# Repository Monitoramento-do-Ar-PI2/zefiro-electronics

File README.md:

# Zefiro electronics
This is the electronic team repository, here you can find the development of embedded system codes, eletronic schematics and pcb layouts.

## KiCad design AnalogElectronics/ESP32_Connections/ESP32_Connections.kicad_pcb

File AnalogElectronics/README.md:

<h1 align="center">
      Eletrônica Analógica Zéfiro
</h1>

<p align="justify">
      A eletrônica analógica é aplicada na estação de monitoramento de ar Zéfiro, sendo um sistema de instrumentação eletrônica modular, onde seus componentes são distríbuidos no melhor posicionamento para seu uso e as ligações realizadas, por meio de cabos, com a central de controle, utilizando o microcontrolador ESP32.

 - **Esquemático Geral** O esquemático geral representa todos os módulos e suas conexões entre si, enquanto cada pasta tem o desenvolvimento individual do esqumático e layout de pcb destes módulos.

  #### Desenvolvedores:
  Clara Justa
  
  Débora Janini
  
  Felipe Alcântara

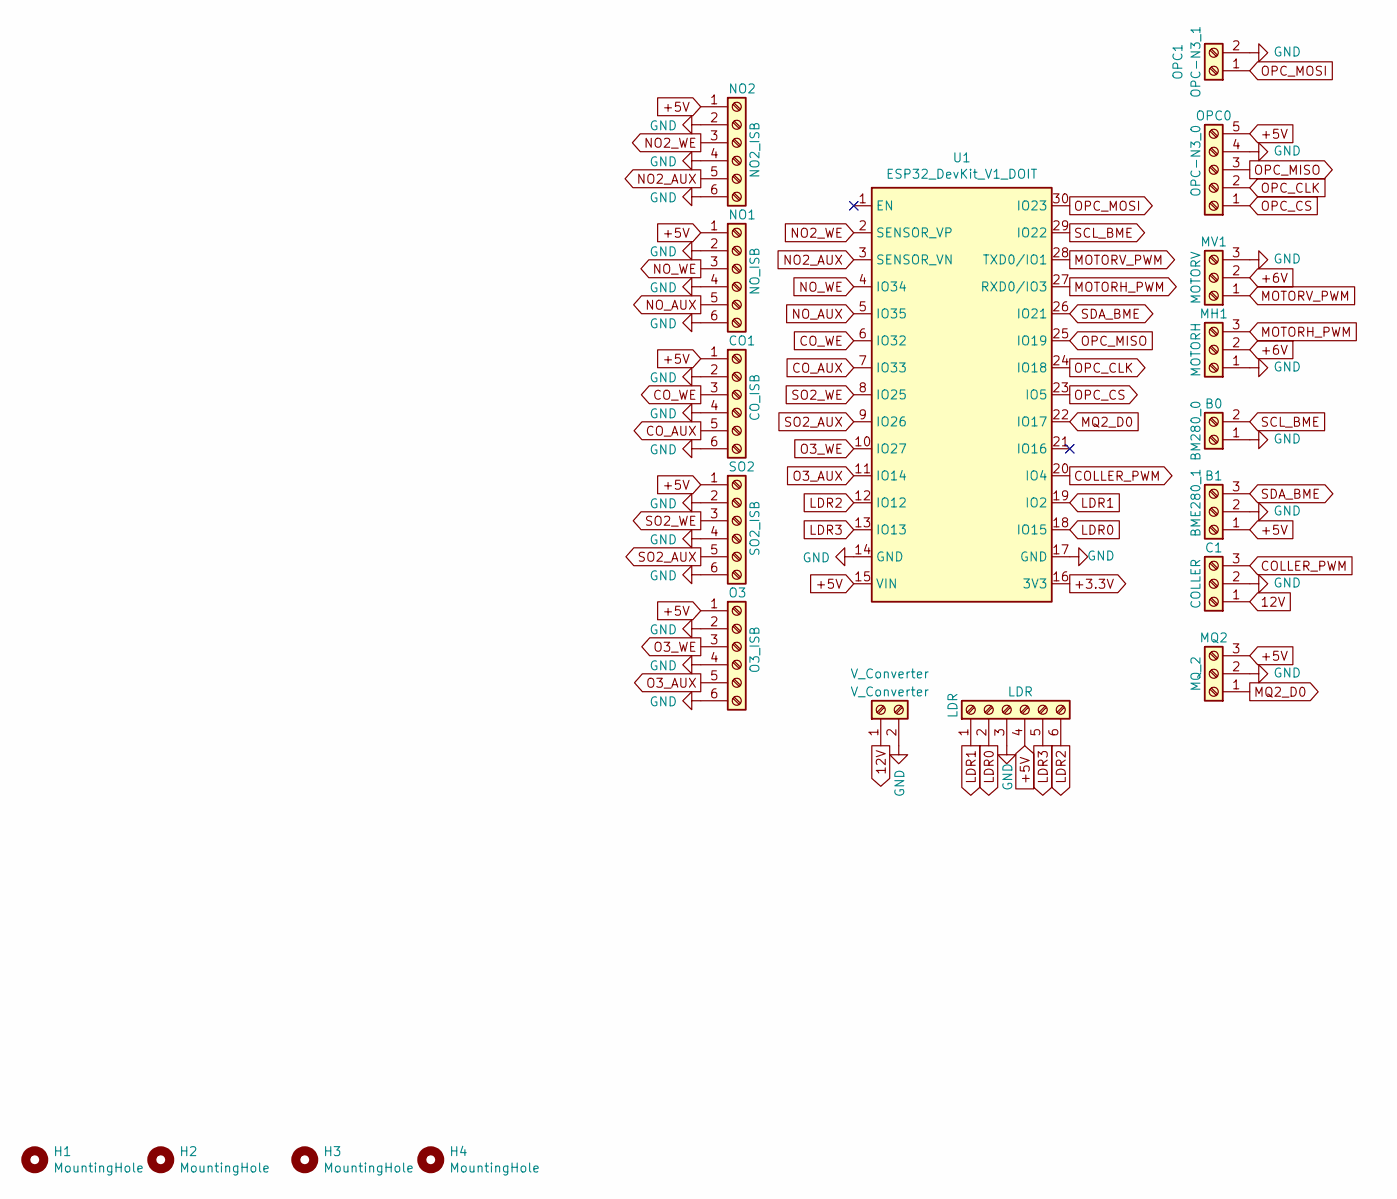
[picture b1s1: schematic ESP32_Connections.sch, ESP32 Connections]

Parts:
B0: BM280_0; Molex_KK-254_AE-6410-02A_1x02_P2.54mm_Vertical
B1: BME280_1; Molex_KK-254_AE-6410-03A_1x03_P2.54mm_Vertical
C1: COLLER; Molex_KK-254_AE-6410-03A_1x03_P2.54mm_Vertical
CO1: CO_ISB; Molex_KK-254_AE-6410-06A_1x06_P2.54mm_Vertical
H1, H2, H3, H4: MountingHole; MountingHole_3mm
LDR: LDR; Molex_KK-254_AE-6410-06A_1x06_P2.54mm_Vertical
MH1: MOTORH; Molex_KK-254_AE-6410-03A_1x03_P2.54mm_Vertical
MQ2: MQ_2; Molex_KK-254_AE-6410-03A_1x03_P2.54mm_Vertical
MV1: MOTORV; Molex_KK-254_AE-6410-03A_1x03_P2.54mm_Vertical
NO1: NO_ISB; Molex_KK-254_AE-6410-06A_1x06_P2.54mm_Vertical
NO2: NO2_ISB; Molex_KK-254_AE-6410-06A_1x06_P2.54mm_Vertical
O3: O3_ISB; Molex_KK-254_AE-6410-06A_1x06_P2.54mm_Vertical
OPC0: OPC-N3_0; Molex_KK-254_AE-6410-05A_1x05_P2.54mm_Vertical
OPC1: OPC-N3_1; Molex_KK-254_AE-6410-02A_1x02_P2.54mm_Vertical
SO2: SO2_ISB; Molex_KK-254_AE-6410-06A_1x06_P2.54mm_Vertical
U1: ESP32_DevKit_V1_DOIT; esp32_devkit_v1_doit
V_Converter: V_Converter; Molex_KK-254_AE-6410-02A_1x02_P2.54mm_Vertical

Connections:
12V: C1.1, V_Converter.1; also elsewhere on the board
+3.3V: U1.16 (3V3)
COLLER_PWM: C1.3, U1.20 (IO4)
CO_AUX: CO1.5, U1.7 (IO33)
CO_WE: CO1.3, U1.6 (IO32)
GND: B0.1, B1.2, C1.2, CO1.2, CO1.4, CO1.6, LDR.3, MH1.1, MQ2.2, MV1.3, NO1.2, NO1.4, NO1.6, NO2.2, NO2.4, NO2.6, O3.2, O3.4, O3.6, OPC0.4, OPC1.2, SO2.2, SO2.4, SO2.6, U1.14 (GND), U1.17 (GND), V_Converter.2; also elsewhere on the board
LDR0: LDR.2, U1.18 (IO15); also elsewhere on the board
LDR1: LDR.1, U1.19 (IO2); also elsewhere on the board
LDR2: LDR.6, U1.12 (IO12); also elsewhere on the board
LDR3: LDR.5, U1.13 (IO13); also elsewhere on the board
MOTORH_PWM: MH1.3, U1.27 (RXD0/IO3)
MOTORV_PWM: MV1.1, U1.28 (TXD0/IO1)
MQ2_D0: MQ2.1, U1.22 (IO17)
NO2_AUX: NO2.5, U1.3 (SENSOR_VN)
NO2_WE: NO2.3, U1.2 (SENSOR_VP)
NO_AUX: NO1.5, U1.5 (IO35)
NO_WE: NO1.3, U1.4 (IO34)
O3_AUX: O3.5, U1.11 (IO14)
O3_WE: O3.3, U1.10 (IO27)
OPC_CLK: OPC0.2, U1.24 (IO18)
OPC_CS: OPC0.1, U1.23 (IO5)
OPC_MISO: OPC0.3, U1.25 (IO19)
OPC_MOSI: OPC1.1, U1.30 (IO23)
SCL_BME: B0.2, U1.29 (IO22)
SDA_BME: B1.3, U1.26 (IO21)
SO2_AUX: SO2.5, U1.9 (IO26)
SO2_WE: SO2.3, U1.8 (IO25)

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
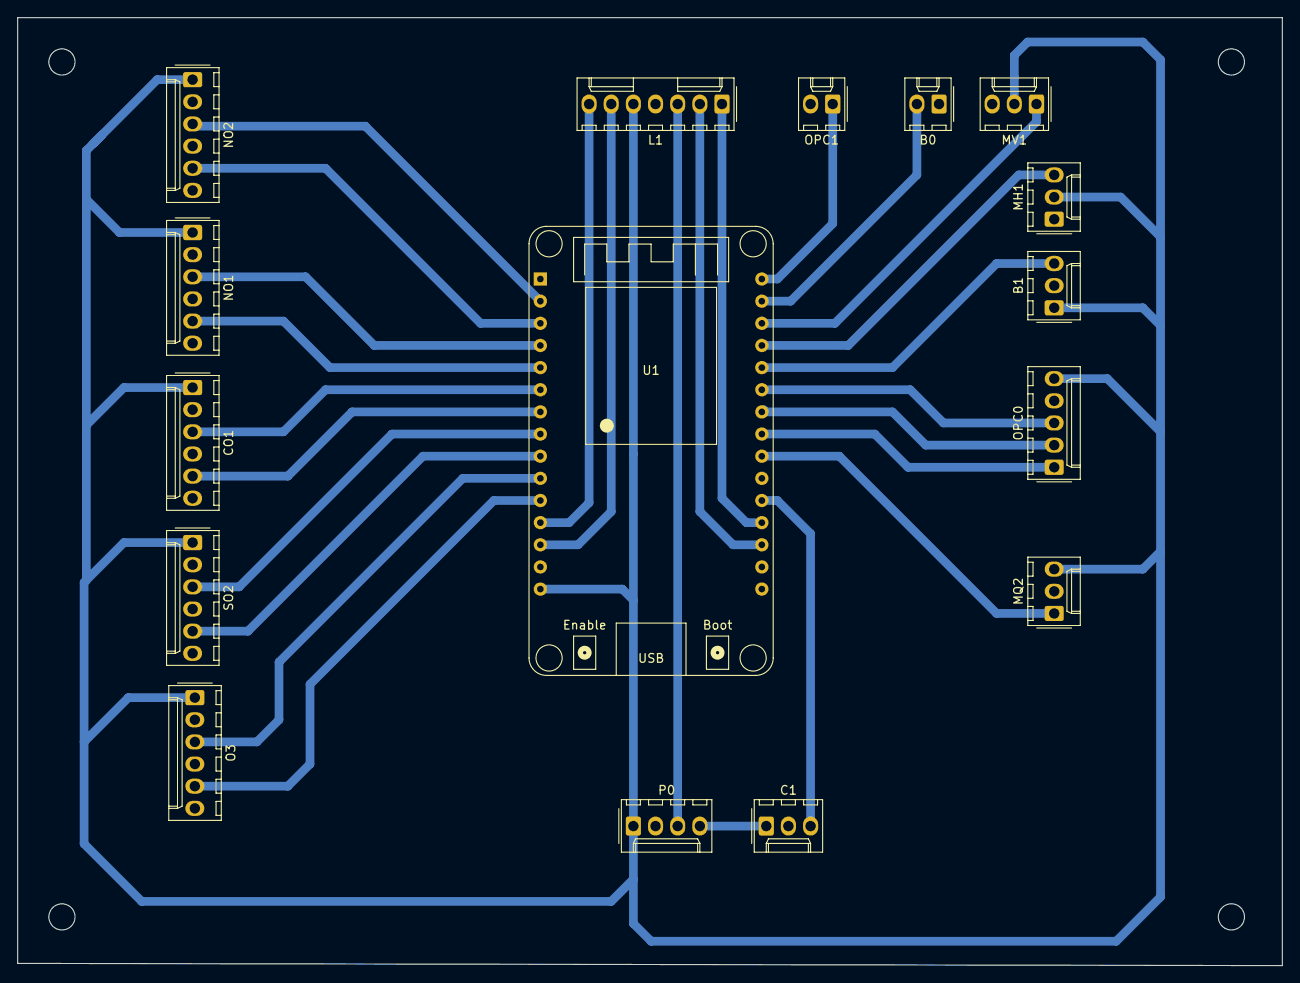
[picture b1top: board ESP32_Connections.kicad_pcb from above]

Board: 2 copper layers, 145.0 x 108.7 mm, 20 parts (0 on the bottom side), 28 nets.

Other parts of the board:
L1: LDRs; Molex_KK-254_AE-6410-07A_1x07_P2.54mm_Vertical
P0: POWER INPUT; Molex_KK-254_AE-6410-04A_1x04_P2.54mm_Vertical

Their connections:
12V: P0.4; also elsewhere on the board
-5V: L1.3, P0.3
GND: L1.4, P0.2; also elsewhere on the board
LDR0: L1.2; also elsewhere on the board
LDR1: L1.1; also elsewhere on the board
LDR2: L1.7; also elsewhere on the board
LDR3: L1.6; also elsewhere on the board

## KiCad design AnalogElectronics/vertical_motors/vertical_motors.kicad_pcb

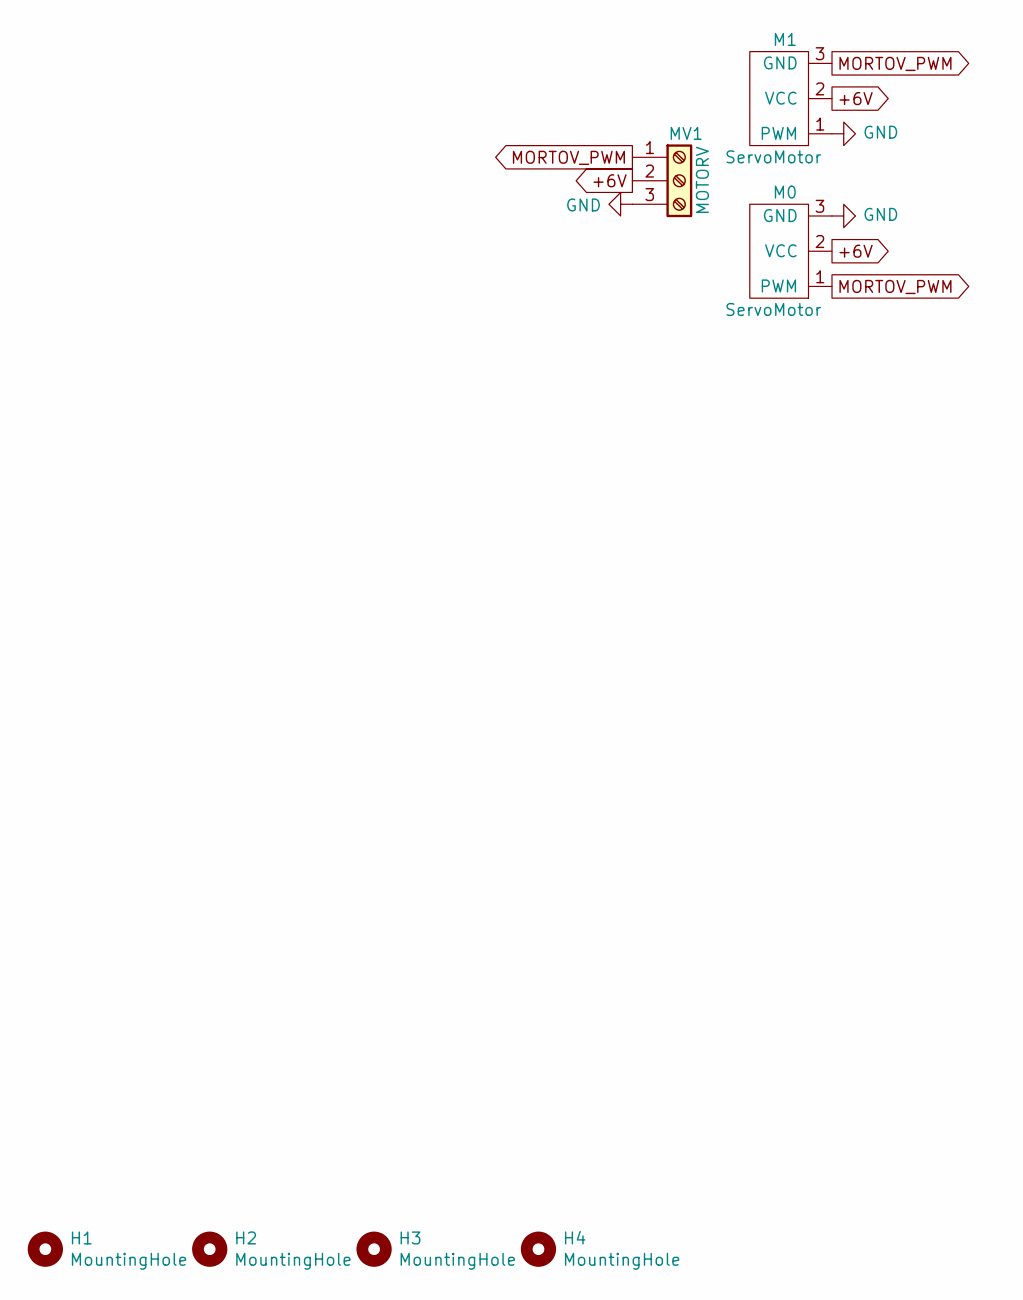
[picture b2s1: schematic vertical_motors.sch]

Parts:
H1, H2, H3, H4: MountingHole; MountingHole_3mm
M0, M1: ServoMotor; Molex_KK-254_AE-6410-03A_1x03_P2.54mm_Vertical
MV1: MOTORV; Molex_KK-254_AE-6410-03A_1x03_P2.54mm_Vertical

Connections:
+5V: M0.2 (VCC), M1.2 (VCC), MV1.2
GND: M0.3 (GND), M1.1 (PWM), MV1.3
MORTOV_PWM: M0.1 (PWM), M1.3 (GND), MV1.1

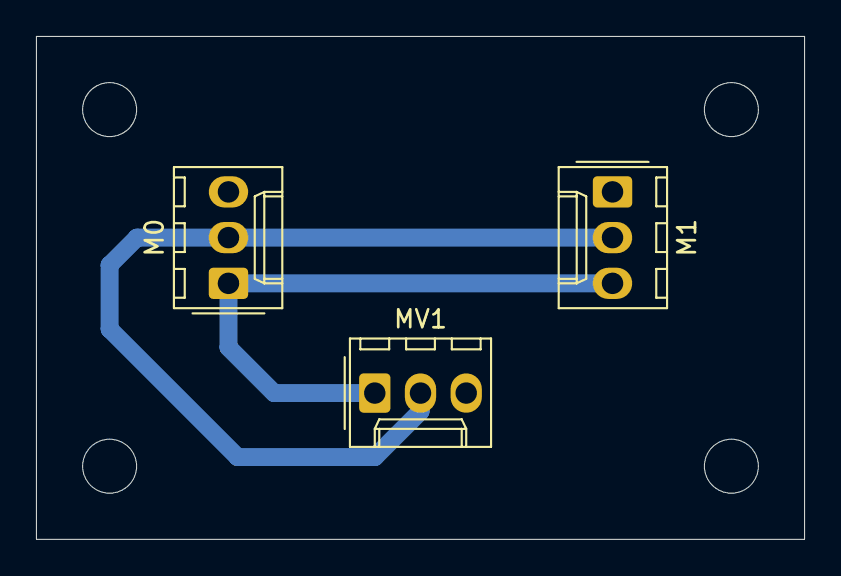
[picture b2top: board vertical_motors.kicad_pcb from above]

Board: 2 copper layers, 42.7 x 27.9 mm, 7 parts (0 on the bottom side), 3 nets.

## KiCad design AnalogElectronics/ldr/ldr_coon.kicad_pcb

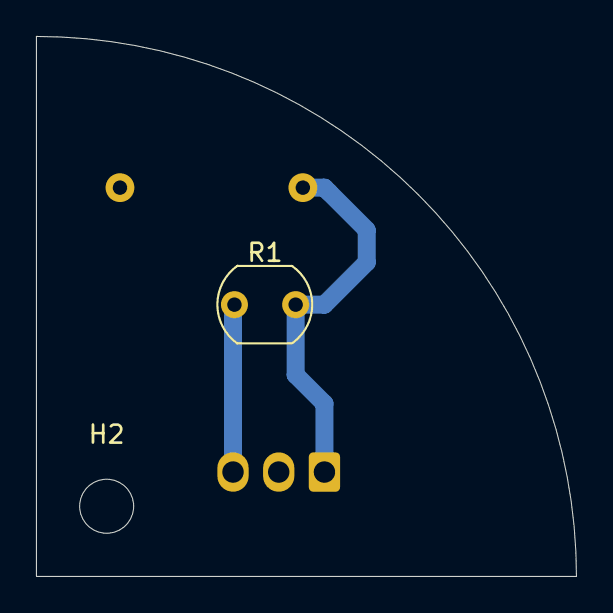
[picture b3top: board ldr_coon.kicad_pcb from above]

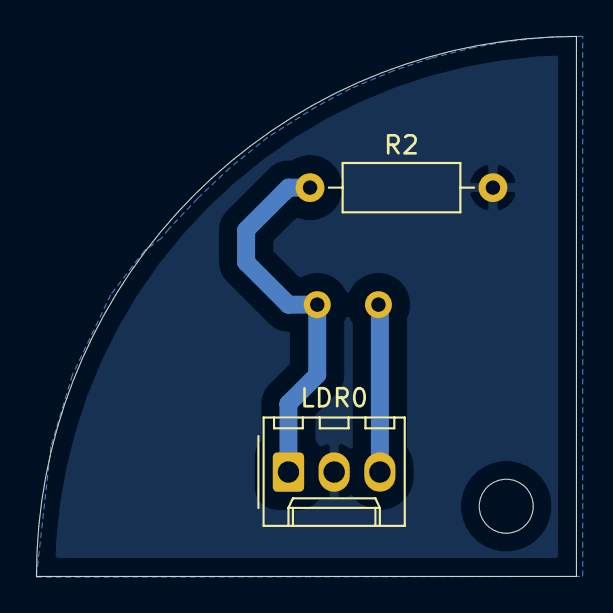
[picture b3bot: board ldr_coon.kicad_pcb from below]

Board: 2 copper layers, 30.0 x 30.0 mm, 4 parts (2 on the bottom side), 3 nets.

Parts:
H2: MountingHole; MountingHole_3mm
LDR0: LDR0; Molex_KK-254_AE-6410-03A_1x03_P2.54mm_Vertical
R1: LDR; R_LDR_5.1x4.3mm_P3.4mm_Vertical
R2: 1k; R_Axial_DIN0207_L6.3mm_D2.5mm_P10.16mm_Horizontal

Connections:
+5V: LDR0.3, R1.1
GND: LDR0.2, R2.2
LDR0: LDR0.1, R1.2, R2.1

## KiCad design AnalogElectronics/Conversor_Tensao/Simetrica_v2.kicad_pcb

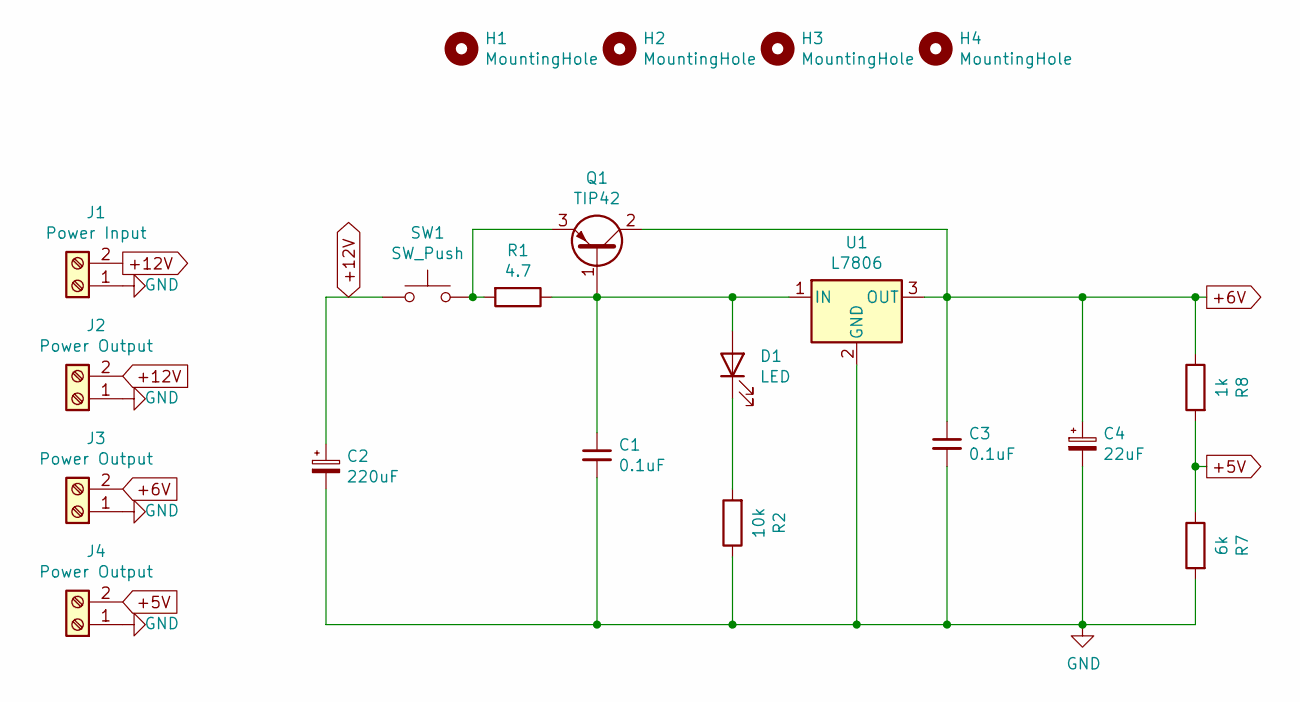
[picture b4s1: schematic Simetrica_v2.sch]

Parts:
C1, C3: 0.1uF; C_Disc_D6.0mm_W2.5mm_P5.00mm
C2: 220uF; C_Radial_D6.3mm_H11.0mm_P2.50mm
C4: 22uF; C_Radial_D6.3mm_H11.0mm_P2.50mm
D1: LED; LED_D3.0mm
H1, H2, H3, H4: MountingHole; MountingHole_2mm
J1: Power Input; PhoenixContact_MSTBA_2,5_2-G-5,08_1x02_P5.08mm_Horizontal
J2, J3, J4: Power Output; Molex_KK-254_AE-6410-02A_1x02_P2.54mm_Vertical
Q1: TIP42; TO-220-3_Vertical
R1: 4.7; R_Axial_DIN0207_L6.3mm_D2.5mm_P10.16mm_Horizontal
R2: 10k; R_Axial_DIN0207_L6.3mm_D2.5mm_P10.16mm_Horizontal
R7: 6k; R_Axial_DIN0207_L6.3mm_D2.5mm_P10.16mm_Horizontal
R8: 1k; R_Axial_DIN0207_L6.3mm_D2.5mm_P10.16mm_Horizontal
SW1: SW_Push; SW_DIP_SPSTx01_Slide_9.78x4.72mm_W7.62mm_P2.54mm
U1: L7806; TO-220-3_Vertical

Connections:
+5V: J4.2, R7.1, R8.2
+6V: C3.1, C4.1, J3.2, Q1.2 (C), R8.1, U1.3 (OUT)
+12V: C2.1, J1.2, J2.2, SW1.1
GND: C1.2, C2.2, C3.2, C4.2, J1.1, J2.1, J3.1, J4.1, R2.1, R7.2, U1.2 (GND)
unnamed: C1.1, D1.2 (A), Q1.1 (B), R1.1, U1.1 (IN)
unnamed: D1.1 (K), R2.2
unnamed: Q1.3 (E), R1.2, SW1.2

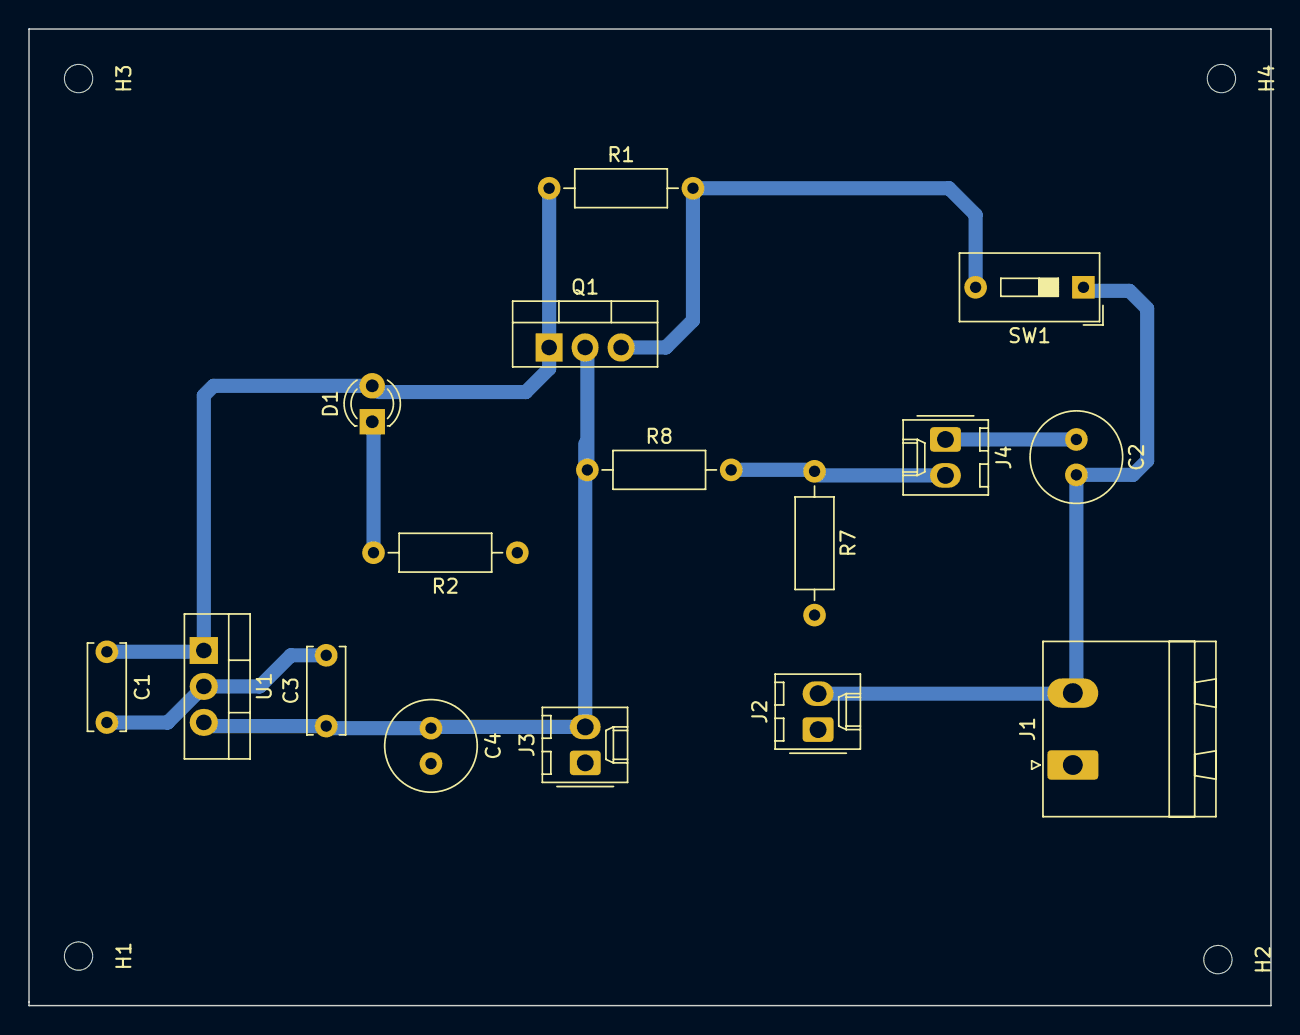
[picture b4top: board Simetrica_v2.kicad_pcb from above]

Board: 2 copper layers, 87.8 x 69.0 mm, 20 parts (0 on the bottom side), 7 nets.

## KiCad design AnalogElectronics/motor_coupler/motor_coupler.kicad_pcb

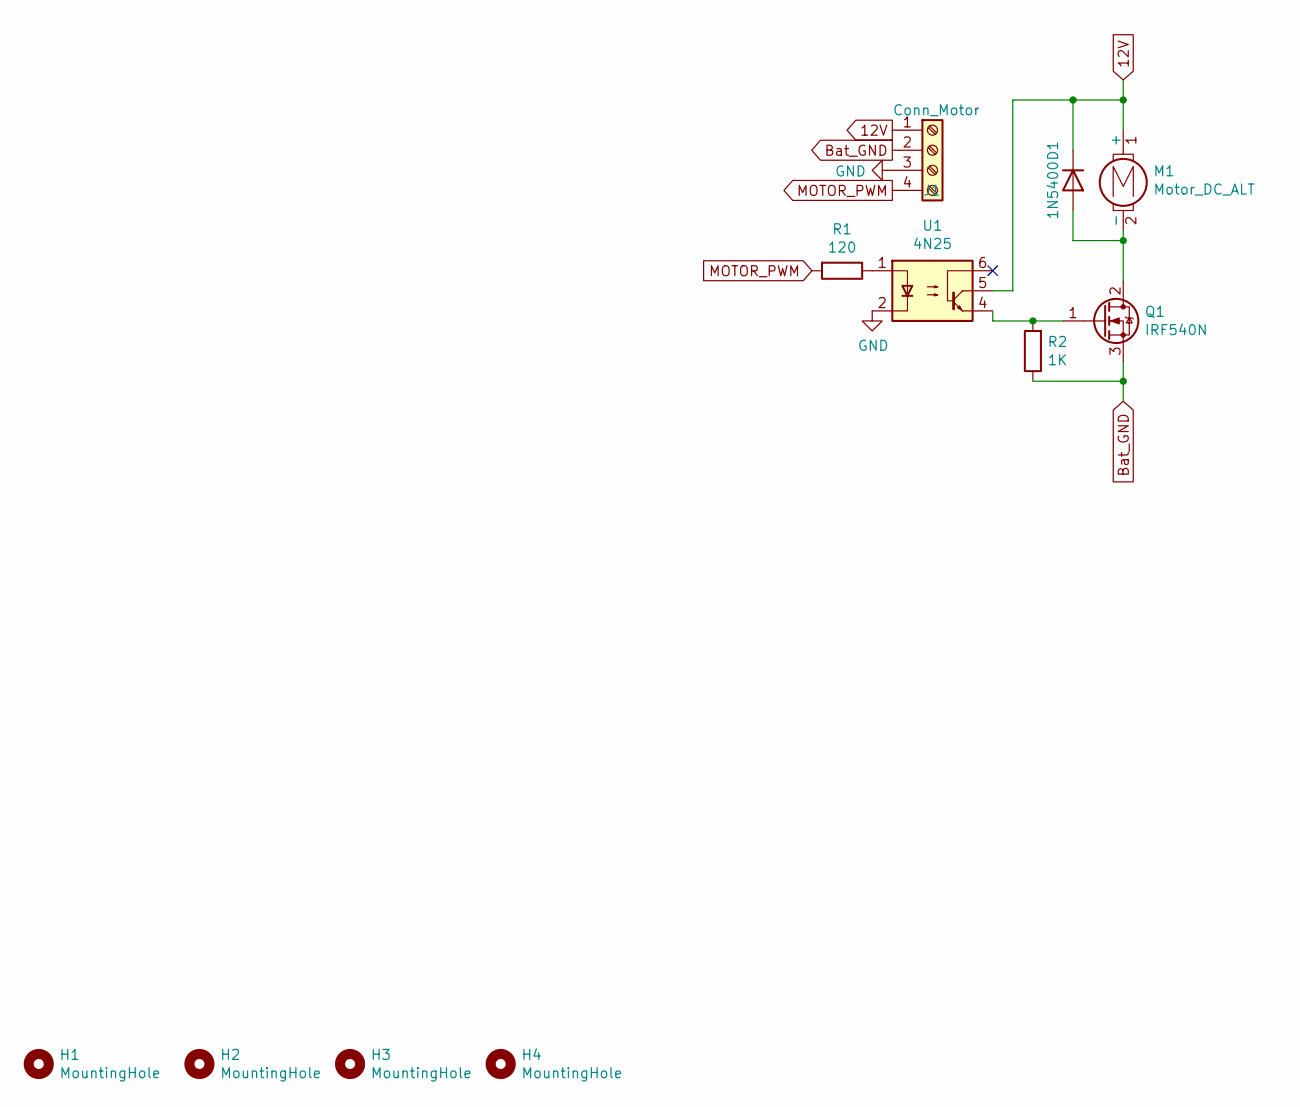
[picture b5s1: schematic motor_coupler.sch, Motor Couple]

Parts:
D1: 1N5400; D_DO-201AD_P15.24mm_Horizontal
H1, H2, H3, H4: MountingHole; MountingHole_3mm
J1: Conn_Motor; Molex_KK-254_AE-6410-04A_1x04_P2.54mm_Vertical
M1: Motor_DC_ALT; Molex_KK-254_AE-6410-02A_1x02_P2.54mm_Vertical
Q1: IRF540N; TO-220-3_Vertical
R1: 120; R_Axial_DIN0207_L6.3mm_D2.5mm_P10.16mm_Horizontal
R2: 1K; R_Axial_DIN0207_L6.3mm_D2.5mm_P10.16mm_Horizontal
U1: 4N25; DIP-6_W7.62mm

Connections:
12V: D1.1 (K), J1.1, M1.1 (+), U1.5
Bat_GND: J1.2, Q1.3 (S), R2.1
GND: J1.3, U1.2
MOTOR_PWM: J1.4, R1.2
unnamed: D1.2 (A), M1.2 (-), Q1.2 (D)
unnamed: Q1.1 (G), R2.2, U1.4
unnamed: R1.1, U1.1

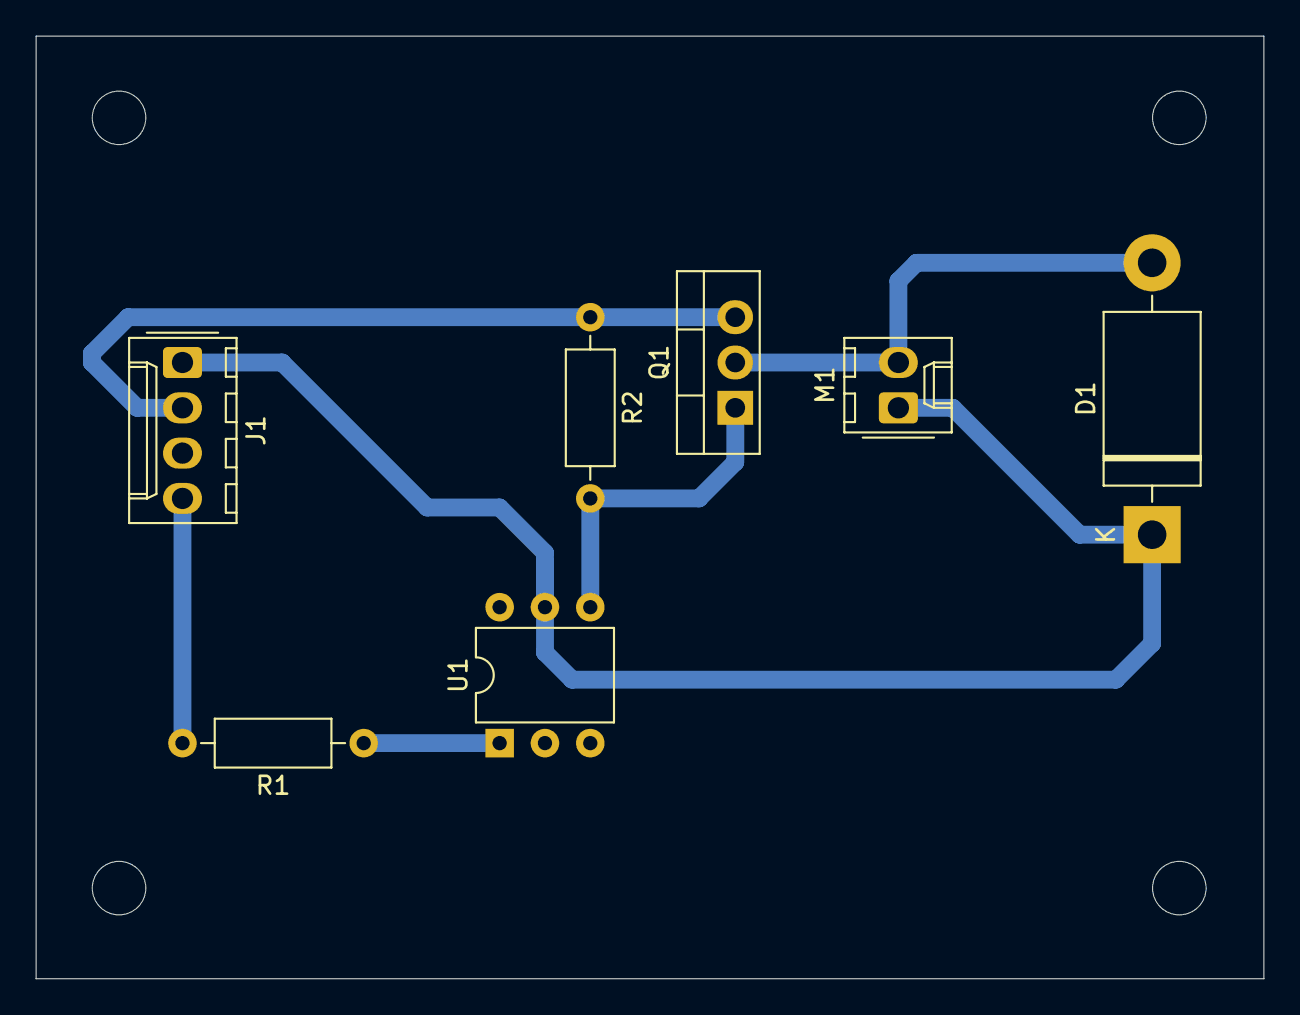
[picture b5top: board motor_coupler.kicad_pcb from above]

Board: 2 copper layers, 68.8 x 52.8 mm, 11 parts (0 on the bottom side), 7 nets.

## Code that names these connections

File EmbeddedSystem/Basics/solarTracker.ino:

/*
Project: Solar Tracker
By: Felipe L. A.
Organization: Zefiro
*/
#include <Servo.h>

#define LDR0 (18)
#define LDR1 (19)
#define LDR2 (12)
#define LDR3 (13)

#define MOTORH (27)
#define MOTORV (28)

Servo Hservo; // Horizontal Servo motor
Servo Vservo; // Vertical Servo motor

int begin_HS = 175;
int begin_VS = 15;

int HS_toplimit = 175;
int VS_toplimit = 75;

int HS_downlimit = 5;
int VS_dowlimit = 15;

int servov = 0;
int servoh = 0;

void setup(){
    Hservo.attach(MOTORH);
    Vservo.attach(MOTORV);
    Hservo.write(begin_HS);
    Vservo.write(begin_VS);
    pinMode(LDR0, INPUT);
    pinMode(LDR1, INPUT);
    pinMode(LDR2, INPUT);
    pinMode(LDR3, INPUT);
    delay(100);
}

void loop() {

    int topLeft   = analogRead(LDR0); 
    int topRight  = analogRead(LDR1); 
    int downLeft  = analogRead(LDR2); 
    int downRight = analogRead(LDR3); 

    int tol = 90; 

    int av_top   = (topLeft + topRight)/2;   // average value top
    int av_down  = (downLeft + downRight)/2; // average value down
    int av_left  = (topLeft + downLeft)/2;   // average value left
    int av_right = (topRight + downRight)/2; // average value right
    int dif_vert = av_top - av_down;   // check the diffirence of up and down
    int dif_hori = av_left - av_right; // check the diffirence og left and rigt

    if (-1*tol > dvert || dvert > tol){
        if (avt > avd){
            servov = ++servov;
            if (servov > VS_toplimit){
                servov = VS_toplimit;}
            }
            else if (avt < avd){
                servov= --servov;
                if (servov < VS_dowlimit){
                    servov = VS_dowlimit;
                }
            }
        Vservo.write(servov);
    }
    if (-1*tol > dhoriz || dhoriz > tol){ // check if the diffirence is in the tolerance else change horizontal angle
        if (avl > avr){
            servoh = --servoh;
            if (servoh < HS_downlimit){
                servoh = HS_downlimit;
            }
        }
        else if (avl < avr){
            servoh = ++servoh;
            if (servoh > HS_toplimit){
                servoh = HS_toplimit;
        }
    }
        else if (avl = avr){
            delay(100);
        }
        Hservo.write(servoh);
    }   
    delay(100);
 
}

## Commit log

2020-11-20 reup files
2020-11-20 README updates
2020-11-20 Updating
2020-11-20 Updating and creating files
2020-11-20 Updating embedded systems
    Submitting subsystem development codes
2020-11-21 Gas and Json update
2020-11-29 Create solarTracker
2020-11-29 Update solarTracker
